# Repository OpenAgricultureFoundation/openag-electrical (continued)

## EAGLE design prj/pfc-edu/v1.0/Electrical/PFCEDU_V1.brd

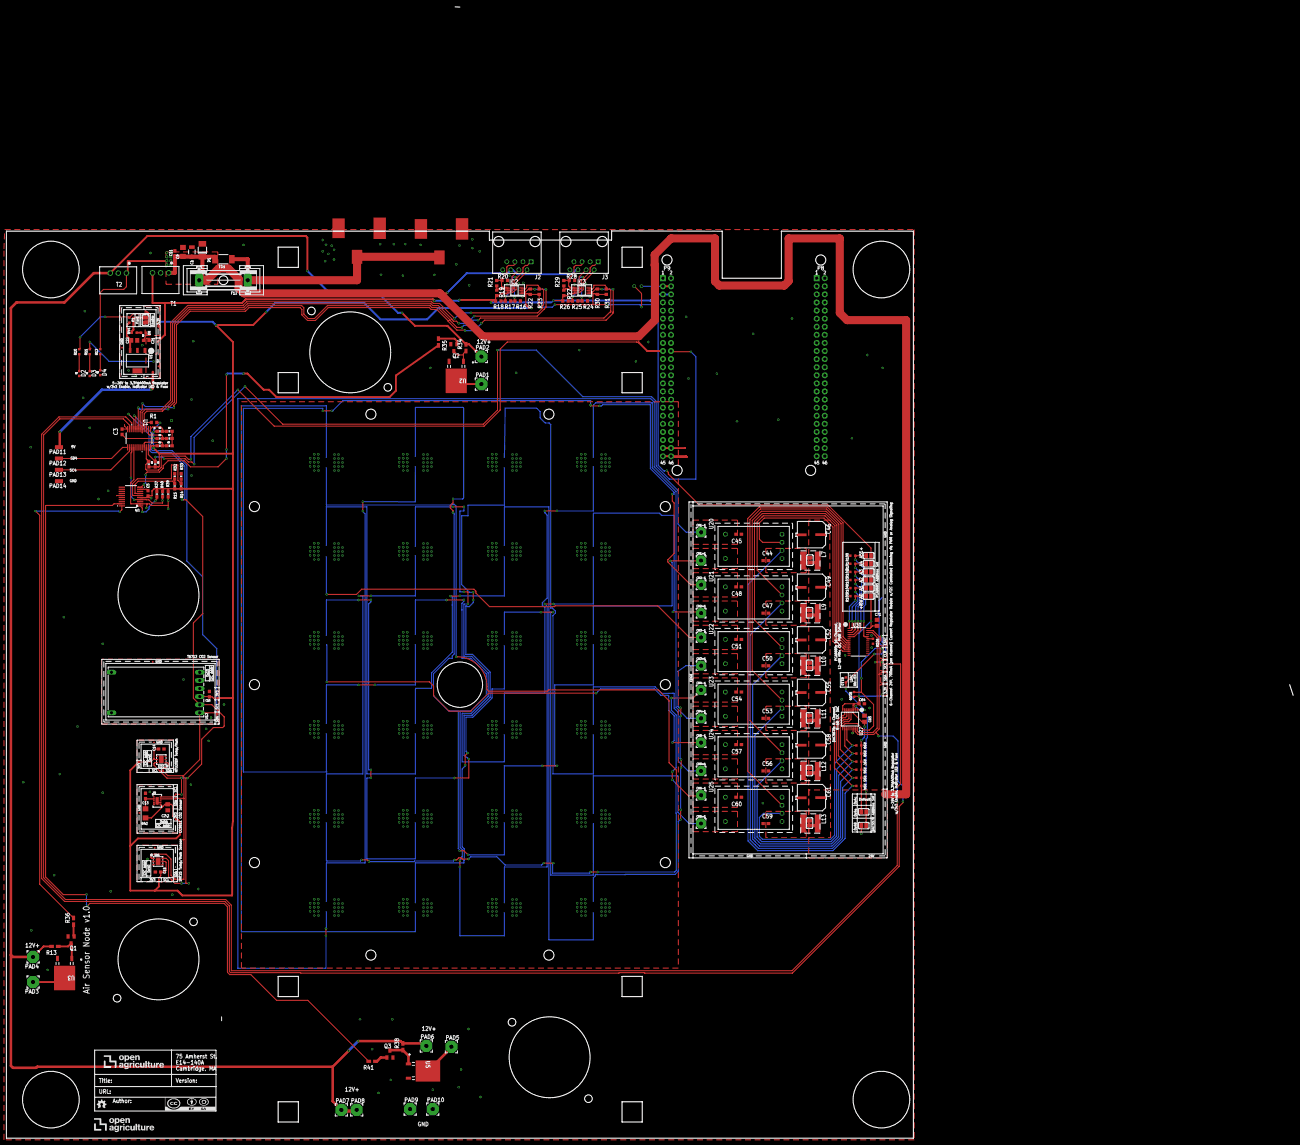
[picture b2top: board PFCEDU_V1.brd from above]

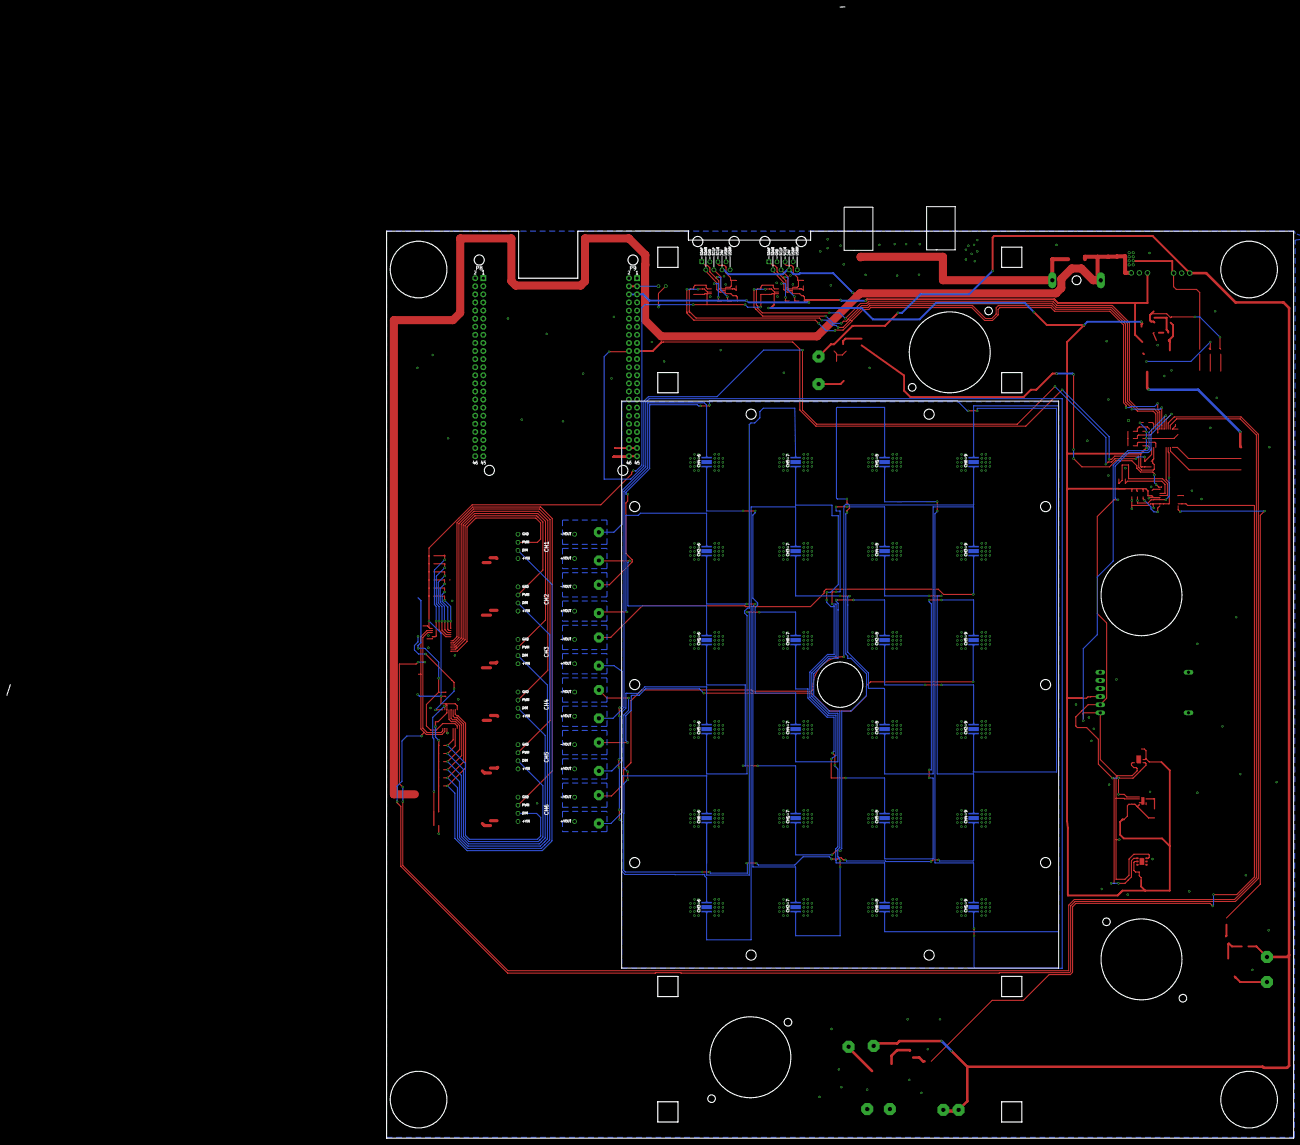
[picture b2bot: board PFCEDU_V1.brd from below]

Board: 2 copper layers, 284.7 x 284.8 mm, 221 parts (24 on the bottom side), 114 nets.

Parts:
ATTRIBUTES: DOCFIELD
C1: 4.7uF; CAP_C1206
C2\2, C65: 4.7uF; C0805
C3, C5, C11: .1uF; C0603@1
C9: 10uF; C1206
C13, C14, C15, C16, C21, C64: 0.1uF; C0603
C22, C71: 10uF; C0805
C44, C45, C47, C48, C50, C51, C53, C54, C56, C57, C59, C60: 10nF; C0603
C46, C49, C52, C55, C58, C61: 100uF; EEE-1HA101UP
CH1+1, CH1-1, CH2+1, CH2-1, CH3+1, CH3-1, CH4+1, CH4-1, CH5+1, CH5-1, CH6+1, CH6-1: 3,17/1,3
CH1-6, CH1-7, CH1-8, CH1-9, CH2-6, CH2-7, CH2-8, CH2-9, CH3-6, CH3-7, CH3-8, CH3-9, CH4-6, CH4-7, CH4-8, CH4-9, CH5-6, CH5-7, CH5-8, CH5-9, CH6-6, CH6-7, CH6-8, CH6-9: XP-E; CREE-XLAMP-XP-E
D1: SMAJ14A; DO-214AC
D2, D3, D4, D8: APT1608CGCK; CHIPLED_0603
F1: 0448.400MR; 0603
F11: SST 7; SS
F12: GSH15
IC2, IC3: PCA9615DP; SOP50P490X110-10N
J2, J3: 54602-908LF; OPENAG-V1-RJ45
L7, L9, L10, L11, L12, L13: 120uH; 74404064121
PAD1, PAD2, PAD3, PAD4, PAD5, PAD6, PAD7, PAD8, PAD9, PAD10: WIREPAD3,81/1,3; 3,81/1,3
PAD11, PAD12, PAD13, PAD14: SMD1,27-2,54
Q1, Q2, Q3: MMBT2222A; SOT23-BEC
R1, R22, R23, R30, R31: 10K; R0603
R2, R3, R4, R5, R6, R7, R8, R9, R14, R15, R32, R33, R37, R39, R40: 10K; 0603-RES
R10, R11, R12, R44: 100; RC0603N
R13, R34, R35, R36, R38, R41: R0805W
R16, R18, R19, R20, R24, R26, R27, R28: 600; R0603
R17, R21, R25, R29: 120; R0603
R42: 4.7K; R1206
R94, R95, R96, R97, R98, R99, R109: 1K; RC0603N
R100, R101, R102, R103, R104, R105, R106: 10K; RC0603N
R110: 0 OHM; RC0603N
SJ1: SOLDERJUMPER_REFLOW_NOPASTE
SJ_A18, SJ_A19, SJ_A20, SJ_A21, SJ_A22, SJ_A23, SJ_A24, SJ_A25, SJ_A26, SJ_A27, SJ_A28, SJ_A29, SJ_A34, SJ_A35: SOLDERJUMPER_REFLOW_NOPASTE
T1: R-78E5.0-1.0
T2: R-78E12.0-1.0; R-78E5.0-1.0
TP1, TP2, TP3, TP5, TP6, TP7, TP36, TP37, TP38, TP39, TP40, TP41, TP42, TP43, TP44, TP45, TP61, TP62, TP63: TPTP06R; TP06R
U1: TCA9548APWRPW24-M; PW24-M
U2, U3, U5: STD12NF06LT4; DPAK
U4: PCF8574APWRPW20-M; PW20-M
U9: CCS811
U10: HPP845E034R5; HTU20D(F)
U11: SHT25; SHT2X
U12: T6713-5K; T6713
U17: LM2937IMP3.3NOPB; MP04A
U20, U21, U22, U23, U24, U25: RCD-24-0.70/VREF; RCD-24-PINNED
U27: DAC5578SPW; TSSOP16
U30: PCA9685; TSSOP28
U$1, U$3: PJ-036AH
U$2: BEAGLE_BONE_BLACK_CAPE
U$9: OPENAG-LOGO-750-MIL

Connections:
24V_IN: F11.1, F12.1, U$1.1, U$3.1
!LDAC!: R110.2, U27.1
+3V3: C2\2.1, C3.1, C5.1, C14.1, C15.1, C16.1, C64.1, C65.1, C71.1, F1.2, IC2.1, IC3.1, R1.2, R2.2, R4.2, R6.2, R8.2, R9.2, R10.2, R14.2, R15.2, R22.2, R23.2, R30.2, R31.2, R37.2, R39.2, R40.2, R42.2, R94.1, R95.1, R96.1, R97.1, R98.1, R99.1, R109.1, SJ1.2, SJ_A18.1, SJ_A19.1, SJ_A20.1, SJ_A21.1, SJ_A22.1, SJ_A23.1, SJ_A34.1, TP5.TP, TP36.TP, TP41.TP, TP44.TP, TP63.TP, U1.24, U4.5, U9.6, U10.5, U11.5, U12.3, U27.3, U27.8, U30.28, U$2.P9.3, U$2.P9.4
+5V: C21.1, IC2.10, IC3.10, PAD11.1, R11.2, R18.1, R19.2, R26.1, R27.2, T1.3, TP62.TP, U17.1, U$2.P9.5, U$2.P9.6
+12V: PAD2.1, PAD4.1, PAD6.1, PAD7.1, PAD8.1, R13.2, R34.2, R38.2, T2.3
+24V: C1.1, C9.1, C11.1, C46.+, C49.+, C52.+, C55.+, C58.+, C61.+, D1.C, F11.2, F12.2, J2.24V(6), J3.24V(6), L7.1, L9.1, L10.1, L11.1, L12.1, L13.1, R12.2, SJ_A24.2, SJ_A25.2, SJ_A26.2, SJ_A27.2, SJ_A28.2, SJ_A29.2, T1.1, T2.1
A0: R105.2, SJ_A18.2, U30.1
A0_EXT_1: R4.1, R5.2, U1.1
A0_IO: R14.1, R33.2, U4.6
A1: R104.2, SJ_A19.2, U30.2
A1_EXT_1: R6.1, R7.2, U1.2
A1_IO: R15.1, R32.2, U4.7
A2: R103.2, SJ_A20.2, U30.3
A2_EXT_1: R2.1, R3.2, U1.21
A3: R102.2, SJ_A21.2, U30.4
A4: R101.2, SJ_A22.2, U30.5
A5: R100.2, SJ_A23.2, U30.24
ADDR0: SJ_A34.2, SJ_A35.2, U27.2
CH1+: CH1+1.1, CH1-6.A, CH1-6.A@1, U20.6
CH1-: C45.1, CH1-1.1, CH1-9.C, CH1-9.C@1, U20.5
CH2+: CH2+1.1, CH2-6.A, CH2-6.A@1, U21.6
CH2-: C48.1, CH2-1.1, CH2-9.C, CH2-9.C@1, U21.5
CH3+: CH3+1.1, CH3-6.A, CH3-6.A@1, U22.6
CH3-: C51.1, CH3-1.1, CH3-9.C, CH3-9.C@1, U22.5
CH4+: CH4+1.1, CH4-6.A, CH4-6.A@1, U23.6
CH4-: C54.1, CH4-1.1, CH4-9.C, CH4-9.C@1, U23.5
CH5+: CH5+1.1, CH5-6.A, CH5-6.A@1, U24.6
CH5-: C57.1, CH5-1.1, CH5-9.C, CH5-9.C@1, U24.5
CH6+: CH6+1.1, CH6-6.A, CH6-6.A@1, U25.6
CH6-: C60.1, CH6-1.1, CH6-9.C, CH6-9.C@1, U25.5
DAC_!CLR!: R109.2, U27.9
DIM1: R94.2, U20.2, U27.7
DIM2: R95.2, U21.2, U27.6
DIM3: R96.2, U22.2, U27.5
DIM4: R97.2, U23.2, U27.4
DIM5: R98.2, U24.2, U27.10
DIM6: R99.2, U25.2, U27.11
DSCLM0: IC2.6, J2.DSCLM(5), R20.2, R21.1
DSCLM1: IC3.6, J3.DSCLM(5), R28.2, R29.1
DSCLP0: IC2.7, J2.DSCLP(4), R19.1, R21.2
DSCLP1: IC3.7, J3.DSCLP(4), R27.1, R29.2
DSDAM0: IC2.9, J2.DSDAM(2), R16.1, R17.2
DSDAM1: IC3.9, J3.DSDAM(2), R24.1, R25.2
DSDAP0: IC2.8, J2.DSDAP(1), R17.1, R18.2
DSDAP1: IC3.8, J3.DSDAP(1), R25.1, R26.2
GND: C1.2, C2\2.2, C3.2, C5.2, C9.2, C11.2, C13.2, C14.2, C15.2, C16.2, C21.2, C22.2, C44.2, C45.2, C46.-, C47.2, C48.2, C49.-, C50.2, C51.2, C52.-, C53.2, C54.2, C55.-, C56.2, C57.2, C58.-, C59.2, C60.2, C61.-, C64.2, C65.2, C71.2, D1.A, D2.C, D3.C, D4.C, D8.C, IC2.5, IC3.5, J2.GND(3), J3.GND(3), PAD9.1, PAD10.1, PAD14.1, Q1.E, Q2.E, Q3.E, R3.1, R5.1, R7.1, R16.2, R20.1, R24.2, R28.1, R32.1, R33.1, R100.1, R101.1, R102.1, R103.1, R104.1, R105.1, R106.2, R110.1, SJ_A35.1, T1.2, T2.2, TP3.TP, TP37.TP, TP40.TP, TP45.TP, TP61.TP, U1.12, U2.2, U3.2, U4.9, U4.15, U5.2, U9.1, U9.7, U9.EP, U10.2, U11.2, U12.4, U12.6, U17.2, U17.4, U20.4, U21.4, U22.4, U23.4, U24.4, U25.4, U27.14, U30.14, U30.25, U$1.2, U$1.3, U$2.P8.1, U$2.P8.2, U$2.P9.1, U$2.P9.2, U$2.P9.43, U$2.P9.44, U$2.P9.45, U$2.P9.46, U$3.2, U$3.3
MOS1: PAD3.1, U3.3
MOS2: PAD1.1, U2.3
MOS3: PAD5.1, U5.3
unnamed: D3.A, R11.1
unnamed: D4.A, R12.1
unnamed: Q1.C, R13.1, U3.1
unnamed: Q1.B, R36.1
unnamed: D2.A, R10.1
unnamed: R37.1, U4.1
unnamed: Q2.C, R34.1, U2.1
unnamed: Q2.B, R35.1
unnamed: Q3.C, R38.1, U5.1
unnamed: Q3.B, R41.1
unnamed: CH2-8.C, CH2-8.C@1, CH2-9.A, CH2-9.A@1
unnamed: CH2-7.C, CH2-7.C@1, CH2-8.A, CH2-8.A@1
unnamed: CH2-6.C, CH2-6.C@1, CH2-7.A, CH2-7.A@1
unnamed: CH4-8.C, CH4-8.C@1, CH4-9.A, CH4-9.A@1
unnamed: CH4-7.C, CH4-7.C@1, CH4-8.A, CH4-8.A@1
unnamed: CH4-6.C, CH4-6.C@1, CH4-7.A, CH4-7.A@1
unnamed: CH6-8.C, CH6-8.C@1, CH6-9.A, CH6-9.A@1
unnamed: CH6-7.C, CH6-7.C@1, CH6-8.A, CH6-8.A@1
unnamed: C44.1, L7.2, SJ_A24.1, U20.1
unnamed: C47.1, L9.2, SJ_A25.1, U21.1
unnamed: C50.1, L10.2, SJ_A26.1, U22.1
unnamed: C53.1, L11.2, SJ_A27.1, U23.1
unnamed: U9.4, U9.5
unnamed: C13.1, R42.1, U9.2
unnamed: C56.1, L12.2, SJ_A28.1, U24.1
unnamed: C59.1, L13.2, SJ_A29.1, U25.1
unnamed: CH6-6.C, CH6-6.C@1, CH6-7.A, CH6-7.A@1
unnamed: CH1-8.C, CH1-8.C@1, CH1-9.A, CH1-9.A@1
unnamed: CH1-7.C, CH1-7.C@1, CH1-8.A, CH1-8.A@1
unnamed: CH1-6.C, CH1-6.C@1, CH1-7.A, CH1-7.A@1
unnamed: CH3-8.C, CH3-8.C@1, CH3-9.A, CH3-9.A@1
unnamed: CH3-7.C, CH3-7.C@1, CH3-8.A, CH3-8.A@1
unnamed: CH3-6.C, CH3-6.C@1, CH3-7.A, CH3-7.A@1
unnamed: CH5-8.C, CH5-8.C@1, CH5-9.A, CH5-9.A@1
unnamed: CH5-7.C, CH5-7.C@1, CH5-8.A, CH5-8.A@1
unnamed: CH5-6.C, CH5-6.C@1, CH5-7.A, CH5-7.A@1
unnamed: D8.A, R44.1
unnamed: C22.1, F1.1, U17.3
OE: R106.1, U30.23
P0_IO: R35.2, U4.10
P6_IO: R41.2, U4.19
P7_IO: R36.2, U4.20
PWM1: U20.3, U30.12
PWM2: U21.3, U30.11
PWM3: U22.3, U30.10
PWM4: U23.3, U30.9
PWM5: U24.3, U30.8
PWM6: U25.3, U30.7
REG_3V3_400MA: R44.2, SJ1.1
RESET1: R1.1, U1.3
SC0: IC2.4, R23.1, U1.5
SC1: IC3.4, R31.1, U1.7
SC2: TP1.TP, TP7.TP, TP39.TP, TP43.TP, U1.9, U9.10, U10.6, U11.6, U12.2
SC3: U1.11, U27.16, U30.26
SC4: PAD13.1, U1.14
SC5: R39.1, U1.16, U4.2
SCL: R8.1, U1.22, U$2.P9.19
SD0: IC2.2, R22.1, U1.4
SD1: IC3.2, R30.1, U1.6
SD2: TP2.TP, TP6.TP, TP38.TP, TP42.TP, U1.8, U9.9, U10.1, U11.1, U12.1
SD3: U1.10, U27.15, U30.27
SD4: PAD12.1, U1.13
SD5: R40.1, U1.15, U4.4
SDA: R9.1, U1.23, U$2.P9.20
T1: CH1-6.THERM, CH1-7.THERM, CH1-8.THERM, CH1-9.THERM, CH2-6.THERM, CH2-7.THERM, CH2-8.THERM, CH2-9.THERM, CH3-6.THERM, CH3-7.THERM, CH3-8.THERM, CH3-9.THERM, CH4-6.THERM, CH4-7.THERM, CH4-8.THERM, CH4-9.THERM, CH5-6.THERM, CH5-7.THERM, CH5-8.THERM, CH5-9.THERM, CH6-6.THERM, CH6-7.THERM, CH6-8.THERM, CH6-9.THERM

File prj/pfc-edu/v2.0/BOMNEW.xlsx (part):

Part | Value | Device | Package | Description | 3D_PACKAGE | ALLIED_NUMBER | AUTHOR | DESCRIPTION.1 | HEIGHT | MANUFACTURER_NAME | MANUFACTURER_PART_NUMBER | MF | MPN | OC_FARNELL | OC_NEWARK | OTHER_PART_NUMBER | POPULATE | PROD_ID | RS_PART_NUMBER | SUPPLIER_NAME | TITLE | TP_SIGNAL_NAME | URL | VALUE.1 | VENDOR | VER | VERIFIED | Column1
ATTRIBUTES |  | DOCFIELD | DOCFIELD | DOCUMENT FIELD |  |  | DP | PFC EDU |  |  |  |  |  |  |  |  |  |  |  |  | PFC EDU |  | https://github.com/OpenAgInitiative/ |  |  | 2
C1 | 4.7uF | 4.7UF-C1206C475K5PACTU | CAP_C1206 | Kemet - C1206C475K5PACTU - CAP CER 4.7UF 50V X5R 1206 |  |  |  |  |  |  |  |  |  |  |  |  | YES |  |  |  |  |  |  | 4.7uF |  |  | NO
C2\2 | 4.7uF | 4.7UF-CL21A475KBQNNNE | C0805 | Samsung - CL21A475KBQNNNE - CAP CER 4.7UF 50V X5R 0805 |  |  |  |  |  |  |  |  |  |  |  |  | YES |  |  |  |  |  |  | 4.7uF |  |  | NO
C3 | .1uF | C-USC0603 | C0603@1 | CAPACITOR, American symbol
C5 | .1uF | C-USC0603 | C0603@1 | CAPACITOR, American symbol
C9 | 10uF | 10UF-CL31B106KBHNNNE | C1206 | Samsung - CL31B106KBHNNNE - CAP CER 10UF 50V X7R 1206 |  |  |  |  |  |  |  |  |  |  |  |  | YES |  |  |  |  |  |  | 10uF |  |  | NO
C11 | .1uF | C-USC0603 | C0603@1 | CAPACITOR, American symbol
C13 | 0.1uF | 0.1UF-C0603C104K5RACTU | C0603 | Kemet - C0603C104K5RACTU - CAP CER 0.1UF 50V X7R 0603 |  |  |  |  |  |  |  |  |  |  |  |  | YES |  |  |  |  |  |  | 0.1uF |  |  | NO
C14 | 0.1uF | 0.1UF-C0603C104K5RACTU | C0603 | Kemet - C0603C104K5RACTU - CAP CER 0.1UF 50V X7R 0603 |  |  |  |  |  |  |  |  |  |  |  |  | YES |  |  |  |  |  |  | 0.1uF |  |  | NO
C15 | 0.1uF | 0.1UF-C0603C104K5RACTU | C0603 | Kemet - C0603C104K5RACTU - CAP CER 0.1UF 50V X7R 0603 |  |  |  |  |  |  |  |  |  |  |  |  | YES |  |  |  |  |  |  | 0.1uF |  |  | NO
C16 | 0.1uF | 0.1UF-C0603C104K5RACTU | C0603 | Kemet - C0603C104K5RACTU - CAP CER 0.1UF 50V X7R 0603 |  |  |  |  |  |  |  |  |  |  |  |  | YES |  |  |  |  |  |  | 0.1uF |  |  | NO
C21 | 0.1uF | 0.1UF-C0603C104K5RACTU | C0603 | Kemet - C0603C104K5RACTU - CAP CER 0.1UF 50V X7R 0603 |  |  |  |  |  |  |  |  |  |  |  |  | YES |  |  |  |  |  |  | 0.1uF |  |  | NO
C22 | 10uF | 10UF-GMK212BBJ106KG-T | C0805 | Taiyo Yuden - GMK212BBJ106KG-T - CAP CER 10UF 35V X5R 0805 |  |  |  |  |  |  |  |  |  |  |  |  | YES |  |  |  |  |  |  | 10uF |  |  | NO
C44 | 10nF | 10NF-C0603C103K5RACTU | C0603 | KEMET - C0603C103K5RACTU - CAP CER 10000PF 50V X7R 0603 |  |  |  |  |  |  |  |  |  |  |  |  | YES |  |  |  |  |  |  | 10nF |  |  | NO
C45 | 10nF | 10NF-C0603C103K5RACTU | C0603 | KEMET - C0603C103K5RACTU - CAP CER 10000PF 50V X7R 0603 |  |  |  |  |  |  |  |  |  |  |  |  | YES |  |  |  |  |  |  | 10nF |  |  | NO
C46 | 100uF | 100UF-EEE-1HA101UP | EEE-1HA101UP | Panasonic - EEE-1HA101UP - ELECTROLYTIC CAP ALUM 100UF 20% 50V SMD |  |  |  |  |  |  |  |  |  |  |  |  | YES |  |  |  |  |  |  | 100uF |  |  | NO
C47 | 10nF | 10NF-C0603C103K5RACTU | C0603 | KEMET - C0603C103K5RACTU - CAP CER 10000PF 50V X7R 0603 |  |  |  |  |  |  |  |  |  |  |  |  | YES |  |  |  |  |  |  | 10nF |  |  | NO
C48 | 10nF | 10NF-C0603C103K5RACTU | C0603 | KEMET - C0603C103K5RACTU - CAP CER 10000PF 50V X7R 0603 |  |  |  |  |  |  |  |  |  |  |  |  | YES |  |  |  |  |  |  | 10nF |  |  | NO
C49 | 100uF | 100UF-EEE-1HA101UP | EEE-1HA101UP | Panasonic - EEE-1HA101UP - ELECTROLYTIC CAP ALUM 100UF 20% 50V SMD |  |  |  |  |  |  |  |  |  |  |  |  | YES |  |  |  |  |  |  | 100uF |  |  | NO
C50 | 10nF | 10NF-C0603C103K5RACTU | C0603 | KEMET - C0603C103K5RACTU - CAP CER 10000PF 50V X7R 0603 |  |  |  |  |  |  |  |  |  |  |  |  | YES |  |  |  |  |  |  | 10nF |  |  | NO
C51 | 10nF | 10NF-C0603C103K5RACTU | C0603 | KEMET - C0603C103K5RACTU - CAP CER 10000PF 50V X7R 0603 |  |  |  |  |  |  |  |  |  |  |  |  | YES |  |  |  |  |  |  | 10nF |  |  | NO
C52 | 100uF | 100UF-EEE-1HA101UP | EEE-1HA101UP | Panasonic - EEE-1HA101UP - ELECTROLYTIC CAP ALUM 100UF 20% 50V SMD |  |  |  |  |  |  |  |  |  |  |  |  | YES |  |  |  |  |  |  | 100uF |  |  | NO
C53 | 10nF | 10NF-C0603C103K5RACTU | C0603 | KEMET - C0603C103K5RACTU - CAP CER 10000PF 50V X7R 0603 |  |  |  |  |  |  |  |  |  |  |  |  | YES |  |  |  |  |  |  | 10nF |  |  | NO
C54 | 10nF | 10NF-C0603C103K5RACTU | C0603 | KEMET - C0603C103K5RACTU - CAP CER 10000PF 50V X7R 0603 |  |  |  |  |  |  |  |  |  |  |  |  | YES |  |  |  |  |  |  | 10nF |  |  | NO
C55 | 100uF | 100UF-EEE-1HA101UP | EEE-1HA101UP | Panasonic - EEE-1HA101UP - ELECTROLYTIC CAP ALUM 100UF 20% 50V SMD |  |  |  |  |  |  |  |  |  |  |  |  | YES |  |  |  |  |  |  | 100uF |  |  | NO
C56 | 10nF | 10NF-C0603C103K5RACTU | C0603 | KEMET - C0603C103K5RACTU - CAP CER 10000PF 50V X7R 0603 |  |  |  |  |  |  |  |  |  |  |  |  | YES |  |  |  |  |  |  | 10nF |  |  | NO
C57 | 10nF | 10NF-C0603C103K5RACTU | C0603 | KEMET - C0603C103K5RACTU - CAP CER 10000PF 50V X7R 0603 |  |  |  |  |  |  |  |  |  |  |  |  | YES |  |  |  |  |  |  | 10nF |  |  | NO
C58 | 100uF | 100UF-EEE-1HA101UP | EEE-1HA101UP | Panasonic - EEE-1HA101UP - ELECTROLYTIC CAP ALUM 100UF 20% 50V SMD |  |  |  |  |  |  |  |  |  |  |  |  | YES |  |  |  |  |  |  | 100uF |  |  | NO
C59 | 10nF | 10NF-C0603C103K5RACTU | C0603 | KEMET - C0603C103K5RACTU - CAP CER 10000PF 50V X7R 0603 |  |  |  |  |  |  |  |  |  |  |  |  | YES |  |  |  |  |  |  | 10nF |  |  | NO
C60 | 10nF | 10NF-C0603C103K5RACTU | C0603 | KEMET - C0603C103K5RACTU - CAP CER 10000PF 50V X7R 0603 |  |  |  |  |  |  |  |  |  |  |  |  | YES |  |  |  |  |  |  | 10nF |  |  | NO
C61 | 100uF | 100UF-EEE-1HA101UP | EEE-1HA101UP | Panasonic - EEE-1HA101UP - ELECTROLYTIC CAP ALUM 100UF 20% 50V SMD |  |  |  |  |  |  |  |  |  |  |  |  | YES |  |  |  |  |  |  | 100uF |  |  | NO
C64 | 0.1uF | 0.1UF-C0603C104K5RACTU | C0603 | Kemet - C0603C104K5RACTU - CAP CER 0.1UF 50V X7R 0603 |  |  |  |  |  |  |  |  |  |  |  |  | YES |  |  |  |  |  |  | 0.1uF |  |  | NO
C65 | 4.7uF | 4.7UF-CL21A475KBQNNNE | C0805 | Samsung - CL21A475KBQNNNE - CAP CER 4.7UF 50V X5R 0805 |  |  |  |  |  |  |  |  |  |  |  |  | YES |  |  |  |  |  |  | 4.7uF |  |  | NO
C71 | 10uF | 10UF-GMK212BBJ106KG-T | C0805 | Taiyo Yuden - GMK212BBJ106KG-T - CAP CER 10UF 35V X5R 0805 |  |  |  |  |  |  |  |  |  |  |  |  | YES |  |  |  |  |  |  | 10uF |  |  | NO
CH1+1 |  | 3,17/1,3 | 3,17/1,3 | THROUGH-HOLE PAD
CH1-1 |  | 3,17/1,3 | 3,17/1,3 | THROUGH-HOLE PAD
CH1-6 | XP-E | LED_W/THERM-XP-E | CREE-XLAMP-XP-E
CH1-7 | XP-E | LED_W/THERM-XP-E | CREE-XLAMP-XP-E
CH1-8 | XP-E | LED_W/THERM-XP-E | CREE-XLAMP-XP-E
CH1-9 | XP-E | LED_W/THERM-XP-E | CREE-XLAMP-XP-E
CH2+1 |  | 3,17/1,3 | 3,17/1,3 | THROUGH-HOLE PAD
CH2-1 |  | 3,17/1,3 | 3,17/1,3 | THROUGH-HOLE PAD
CH2-6 | XP-E | LED_W/THERM-XP-E | CREE-XLAMP-XP-E
CH2-7 | XP-E | LED_W/THERM-XP-E | CREE-XLAMP-XP-E
CH2-8 | XP-E | LED_W/THERM-XP-E | CREE-XLAMP-XP-E
CH2-9 | XP-E | LED_W/THERM-XP-E | CREE-XLAMP-XP-E
CH3+1 |  | 3,17/1,3 | 3,17/1,3 | THROUGH-HOLE PAD
CH3-1 |  | 3,17/1,3 | 3,17/1,3 | THROUGH-HOLE PAD
CH3-6 | XP-E | LED_W/THERM-XP-E | CREE-XLAMP-XP-E
CH3-7 | XP-E | LED_W/THERM-XP-E | CREE-XLAMP-XP-E
CH3-8 | XP-E | LED_W/THERM-XP-E | CREE-XLAMP-XP-E
CH3-9 | XP-E | LED_W/THERM-XP-E | CREE-XLAMP-XP-E
CH4+1 |  | 3,17/1,3 | 3,17/1,3 | THROUGH-HOLE PAD
CH4-1 |  | 3,17/1,3 | 3,17/1,3 | THROUGH-HOLE PAD
CH4-6 | XP-E | LED_W/THERM-XP-E | CREE-XLAMP-XP-E
CH4-7 | XP-E | LED_W/THERM-XP-E | CREE-XLAMP-XP-E
CH4-8 | XP-E | LED_W/THERM-XP-E | CREE-XLAMP-XP-E
CH4-9 | XP-E | LED_W/THERM-XP-E | CREE-XLAMP-XP-E
CH5+1 |  | 3,17/1,3 | 3,17/1,3 | THROUGH-HOLE PAD
CH5-1 |  | 3,17/1,3 | 3,17/1,3 | THROUGH-HOLE PAD
CH5-6 | XP-E | LED_W/THERM-XP-E | CREE-XLAMP-XP-E
CH5-7 | XP-E | LED_W/THERM-XP-E | CREE-XLAMP-XP-E
CH5-8 | XP-E | LED_W/THERM-XP-E | CREE-XLAMP-XP-E
CH5-9 | XP-E | LED_W/THERM-XP-E | CREE-XLAMP-XP-E
CH6+1 |  | 3,17/1,3 | 3,17/1,3 | THROUGH-HOLE PAD
CH6-1 |  | 3,17/1,3 | 3,17/1,3 | THROUGH-HOLE PAD
CH6-6 | XP-E | LED_W/THERM-XP-E | CREE-XLAMP-XP-E
CH6-7 | XP-E | LED_W/THERM-XP-E | CREE-XLAMP-XP-E
CH6-8 | XP-E | LED_W/THERM-XP-E | CREE-XLAMP-XP-E
CH6-9 | XP-E | LED_W/THERM-XP-E | CREE-XLAMP-XP-E
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
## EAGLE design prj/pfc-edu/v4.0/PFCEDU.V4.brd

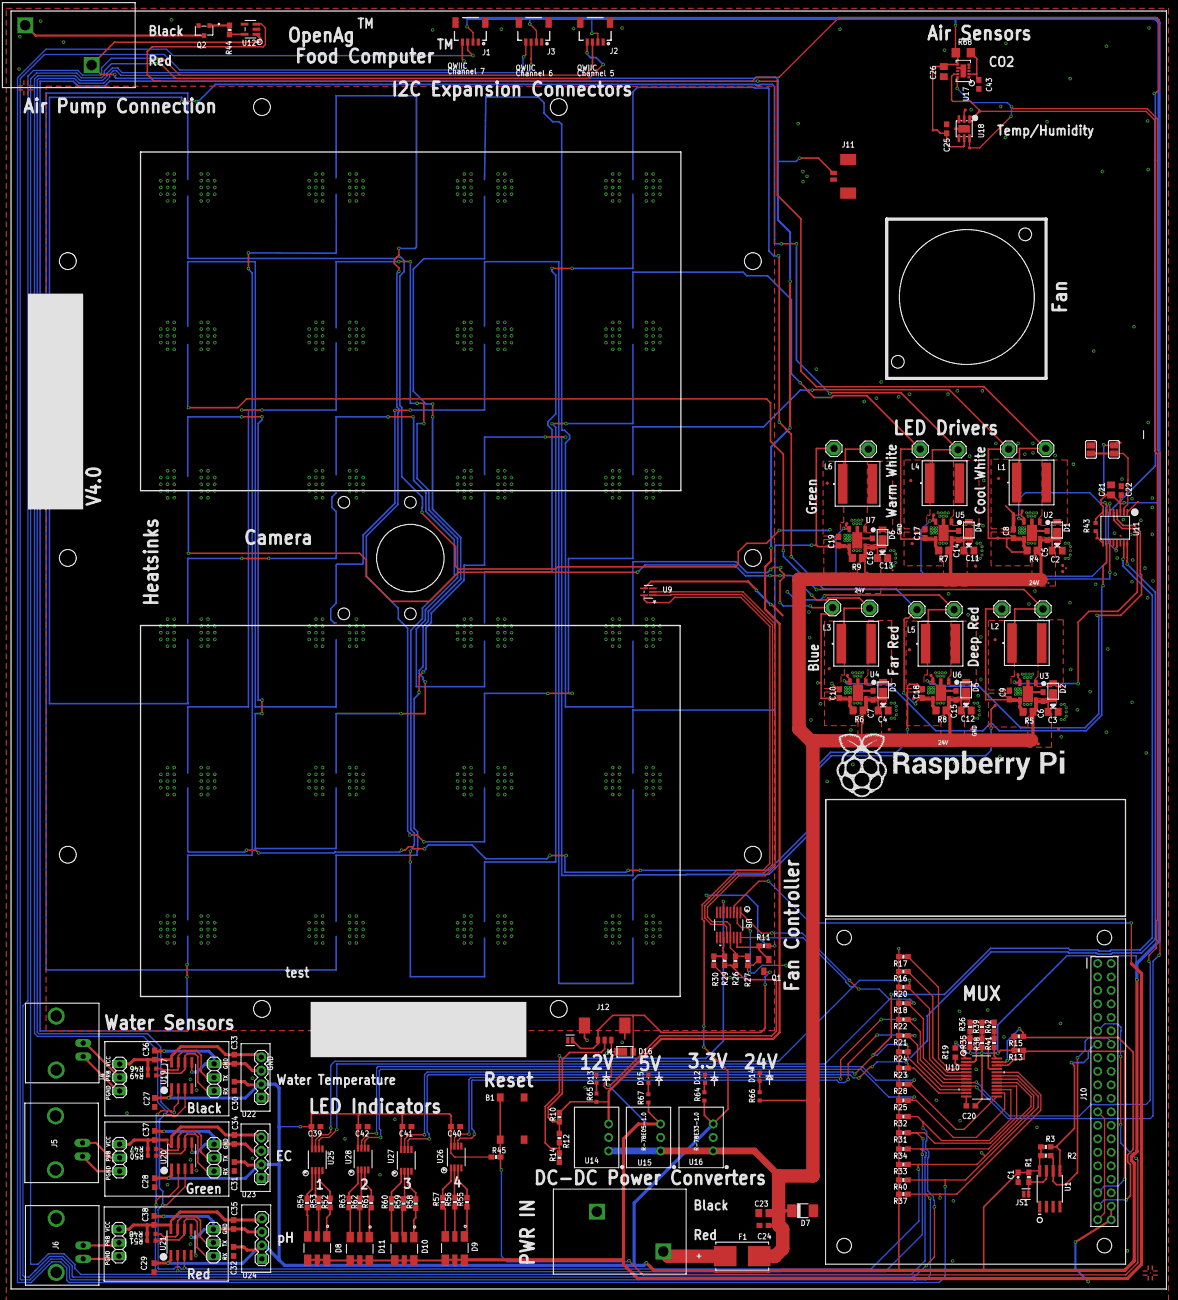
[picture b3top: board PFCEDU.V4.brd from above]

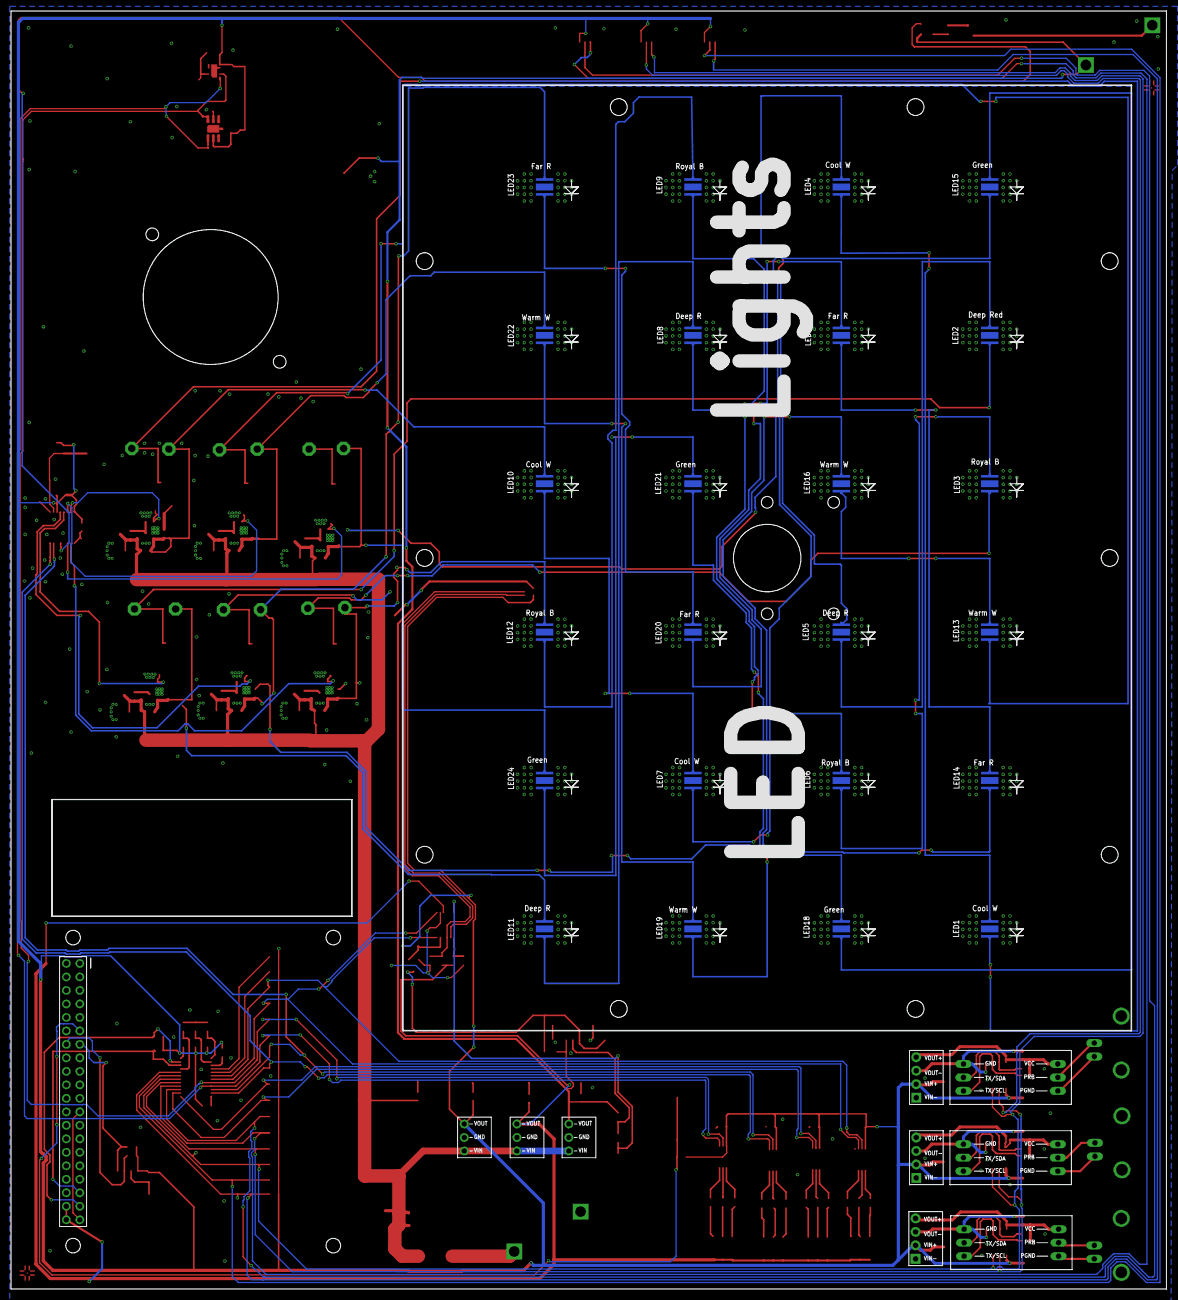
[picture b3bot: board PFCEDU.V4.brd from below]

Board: 2 copper layers, 217.6 x 240.6 mm, 262 parts (24 on the bottom side), 138 nets.

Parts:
A1: PTS645
C1: 0.1uF; CAP-0603
C2, C3, C4, C11, C12, C13: 10uF; C0805
C5, C6, C7, C8, C9, C10, C14, C15, C16, C17, C18, C19, C22, C25, C27, C28, C29, C30, C31, C32, C33, C34, C35, C36, C37, C38, C39, C40, C41, C42, C43: 0.1uF; C0603
C20, C24: .1uF; C0603@1
C21, C23, C26: 4.7uF; C0805
D1, D2, D3, D4, D5, D6, D16: SBR2A40P1-7; POWERDI123
D7: SMAJ14A; DO-214AC
D8, D9, D10, D11: QBLP679E-RGB; LED_QBLP679E-RGB
D12, D13, D14, D15: APT1608; CHIPLED_0603
DRILEGEND: DRILEGEND
F1: 0154005.DR; 0154SERIES
J1, J2, J3: Qwiic Right Angle; 1X04_1MM_RA
J4, J5, J6: 5227161-9; BNC-5227161
J7, J8, J9: ATLAS-STAMP
J10: PFCEDU_V7_PI4_AI_CONNECTORS_2X20-RPI-NOFIRST
J11: MOLEX_2P_1.25MM
J12: MOLEX_3P_1.25MM
JS1, JS2: 1X02-SJ-NO
L1, L2, L3, L4, L5, L6: NR8040T101M; IND_TAIYO_NR8040
LED1, LED2, LED3, LED4, LED5, LED6, LED7, LED8, LED9, LED10, LED11, LED12, LED13, LED14, LED15, LED16, LED17, LED18, LED19, LED20, LED21, LED22, LED23, LED24: XP-E; CREE-XLAMP-XP-E
LSP1, LSP2, LSP3, LSP4, LSP5, LSP6, LSP7, LSP8, LSP9, LSP10, LSP11, LSP12: SE14
Q1: MMBT2222A; SOT23-BEC
Q2: BSS138K; SOT-23
R1: 1K; RES-0603
R2: 2.2kΩ; RES-0603
R3: 2.2KΩ; RES-0603
R4, R5, R6, R7, R8, R9: 6.34 ohm; R0805
R10, R12, R26, R27, R29, R30, R45: 10k; 0603-RES
R11, R14: 4.7KΩ; 0603-RES
R13: 2.2K; 0603-RES
R15, R16, R17, R18, R20, R21, R22, R23, R24, R25, R28, R31, R32, R33, R34, R37, R40: 2.2k; 0603-RES
R19: 10K; R0603
R35, R38, R41: 10K; 0603-RES
R36, R39, R42: NP; 0603-RES
R43: 1K; RC0603N
R44: 10; 0603-RES
R46, R47, R48, R49, R50, R51: 2.2KΩ; RC0603N
R52, R53, R54, R55, R56, R57, R58, R59, R60, R61, R62, R63: 240; 0603-RES
R64: 160; RC0603N
R65: 600; RC0603N
R66: 1200; RC0603N
R67: 260; RC0603N
R68: 10K; R1206
SJ1, SJ2: SJ1
TP38, TP39, TP40, TP41, TP112, TP113, TP114, TP115, TP116, TP117, TP118, TP119, TP120, TP121, TP122, TP123, TP124, TP125, TP126, TP127, TP128, TP129, TP130, TP131, TP132, TP133, TP134, TP135, TP136, TP137, TP138, TP139, TP140, TP141: TPTP06R; TP06R
TP99, TP100, TP101, TP104, TP105, TP106, TP107: TPTP04R; TP04R
U1: 24LC32A; SO08-EIAJ
U2, U3, U4, U5, U6, U7: AL8861
U8: ADT7470ARQZ-REEL; RQ_16
U9: TMP05AKSZ-500RL7; KS_5
U10: TCA9548APWRPW24-M; PW24-M
U11: DAC5578; TSSOP16
U12: UCC27517DBVR; DBV5
U14: R-78E12-1.0; R-78E5.0-1.0
U15: R-78E05-1.0; R-78E5.0-1.0
U16: R-78E33-1.0; R-78E5.0-1.0
U17: CCS811
U18: SHT25; SHT2X
U19, U20, U21: ISO1540; D8
U22, U23, U24: RM-3.33.3S; RM3.33.3S-SIP4
U25, U26, U27, U28: PCA9633DP1SOT505-1-L; SOT505-1-L
U$1, U$2: PASSER-CIRCLE
W11, W12: PHOENIX_2P

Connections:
24V_IN: F1.1, W12.1
!LDAC!: TP104.1, U11.1
+3V3: C1.1, C20.1, C21.1, C22.1, C25.1, C26.1, C27.1, C28.1, C29.1, C30.1, C31.1, C32.1, C39.2, C40.2, C41.2, C42.2, J1.2, J2.2, J3.2, R1.2, R2.2, R3.2, R11.2, R13.2, R15.2, R16.2, R17.2, R18.2, R19.2, R20.2, R21.2, R22.2, R23.2, R24.2, R25.2, R28.2, R31.2, R32.2, R33.2, R34.2, R35.2, R37.2, R38.2, R40.2, R41.2, R43.1, R45.1, R64.2, R68.2, SJ1.1, TP41.TP, TP100.1, U1.8, U9.5, U10.24, U11.3, U11.8, U16.3, U17.6, U18.5, U19.1, U20.1, U21.1, U22.2, U23.2, U24.2, U25.8, U26.8, U27.8, U28.8
+5V: D8.4, D8.5, D8.6, D9.4, D9.5, D9.6, D10.4, D10.5, D10.6, D11.4, D11.5, D11.6, J10.2, J10.4, R26.1, R29.1, R67.2, U8.3, U15.3
+12V: D16.-, J11.2, J12.1, R10.2, R65.2, U12.1, U14.3, W11.2
+24V: C2.1, C3.1, C4.1, C5.1, C6.1, C7.1, C11.1, C12.1, C13.1, C14.1, C15.1, C16.1, C23.1, C24.1, D1.-, D2.-, D3.-, D4.-, D5.-, D6.-, D7.C, F1.2, R4.2, R5.2, R6.2, R7.2, R8.2, R9.2, R66.2, TP99.1, TP113.TP, TP118.TP, TP123.TP, TP128.TP, TP133.TP, TP138.TP, U2.5, U3.5, U4.5, U5.5, U6.5, U7.5, U14.1, U15.1, U16.1
A0_EXT_1: R35.1, R36.2, U10.1
A1_EXT_1: R38.1, R39.2, U10.2
A2_EXT_1: R41.1, R42.2, U10.21
ADDR0: SJ1.2, SJ2.2, U11.2
BUTTON: A1.P$1, A1.P$2, J10.29, R45.2
CH1+: C8.2, LED10.A, LED10.A@1, LSP1.MP, R4.1, TP115.TP, U2.4
CH1-: C8.1, L1.1, LED1.C, LED1.C@1, LSP2.MP, TP112.TP
CH2+: C17.2, LED22.A, LED22.A@1, LSP7.MP, R7.1, TP120.TP, U5.4
CH2-: C17.1, L4.1, LED13.C, LED13.C@1, LSP8.MP, TP117.TP
CH3+: C9.2, LED11.A, LED11.A@1, LSP3.MP, R5.1, TP125.TP, U3.4
CH3-: C9.1, L2.1, LED2.C, LED2.C@1, LSP4.MP, TP122.TP
CH4+: C18.2, LED23.A, LED23.A@1, LSP9.MP, R8.1, TP130.TP, U6.4
CH4-: C18.1, L5.1, LED14.C, LED14.C@1, LSP10.MP, TP127.TP
CH5+: C10.2, LED12.A, LED12.A@1, LSP5.MP, R6.1, TP135.TP, U4.4
CH5-: C10.1, L3.1, LED3.C, LED3.C@1, LSP6.MP, TP132.TP
CH6+: C19.2, LED24.A, LED24.A@1, LSP11.MP, R9.1, TP140.TP, U7.4
CH6-: C19.1, L6.1, LED15.C, LED15.C@1, LSP12.MP, TP137.TP
DAC_!CLR!: R43.2, TP105.1, U11.9
F1_PWM: Q1.B, R11.1, U8.15
FAN_NEG: D16.+, J12.5, JS2.1, Q1.C
GATE: Q2.1, R44.2
GND: A1.P$3, A1.P$4, C1.2, C2.2, C3.2, C4.2, C5.2, C6.2, C7.2, C11.2, C12.2, C13.2, C14.2, C15.2, C16.2, C20.2, C21.2, C22.2, C23.2, C24.2, C25.2, C26.2, C27.2, C28.2, C29.2, C30.2, C31.2, C32.2, C39.1, C40.1, C41.1, C42.1, C43.2, D7.A, D12.C, D13.C, D14.C, D15.C, J1.1, J2.1, J3.1, J10.6, J10.9, J10.14, J10.20, J10.25, J10.30, J10.34, J10.39, J11.1, J11.3, J11.4, J12.3, J12.4, JS1.1, JS2.2, Q1.E, Q2.2, R14.1, R27.2, R30.2, R36.1, R39.1, R42.1, SJ2.1, TP40.TP, TP101.1, TP106.1, TP107.1, TP114.TP, TP119.TP, TP124.TP, TP129.TP, TP134.TP, TP139.TP, U1.1, U1.2, U1.3, U1.4, U2.2, U2.44, U3.2, U3.44, U4.2, U4.44, U5.2, U5.44, U6.2, U6.44, U7.2, U7.44, U8.2, U9.4, U10.12, U11.14, U12.2, U12.4, U14.2, U15.2, U16.2, U17.1, U17.7, U17.EP, U18.2, U19.4, U20.4, U21.4, U22.1, U23.1, U24.1, U25.5, U26.5, U27.5, U28.5, W12.2
ID_SC: J10.28, R2.1, U1.6
ID_SD: J10.27, R3.1, U1.5
ISO_3V3_2: C33.1, C36.1, J7.4, R46.2, R49.2, U19.8, U22.4
ISO_3V3_3: C34.1, C37.1, J8.4, R47.2, R50.2, U20.8, U23.4
ISO_3V3_4: C35.1, C38.1, J9.4, R48.2, R51.2, U21.8, U24.4
ISO_GND_2: C33.2, C36.2, J7.3, U19.5, U22.3
ISO_GND_3: C34.2, C37.2, J8.3, U20.5, U23.3
ISO_GND_4: C35.2, C38.2, J9.3, U21.5, U24.3
ISO_SCL_2: J7.1, R49.1, U19.6
ISO_SCL_3: J8.1, R50.1, U20.6
ISO_SCL_4: J9.1, R51.1, U21.6
ISO_SDA_2: J7.2, R46.1, U19.7
ISO_SDA_3: J8.2, R47.1, U20.7
ISO_SDA_4: J9.2, R48.1, U21.7
LX: D1.+, L1.2, U2.1
LX_2: D4.+, L4.2, U5.1
LX_3: D2.+, L2.2, U3.1
LX_4: D5.+, L5.2, U6.1
LX_5: D3.+, L3.2, U4.1
LX_6: D6.+, L6.2, U7.1
unnamed: R54.2, U25.1
unnamed: D15.A, R67.1
unnamed: R53.2, U25.2
unnamed: D14.A, R66.1
unnamed: R52.2, U25.3
unnamed: D8.3, R54.1
unnamed: D8.2, R53.1
unnamed: D8.1, R52.1
unnamed: R63.2, U28.1
unnamed: R62.2, U28.2
unnamed: R61.2, U28.3
unnamed: D12.A, R64.1
unnamed: D11.3, R63.1
unnamed: D11.2, R62.1
unnamed: D11.1, R61.1
unnamed: R60.2, U27.1
unnamed: R59.2, U27.2
unnamed: R58.2, U27.3
unnamed: D10.3, R60.1
unnamed: D10.2, R59.1
unnamed: D10.1, R58.1
unnamed: R57.2, U26.1
unnamed: R56.2, U26.2
unnamed: R55.2, U26.3
unnamed: D9.3, R57.1
unnamed: D9.2, R56.1
unnamed: D9.1, R55.1
unnamed: LED13.A, LED13.A@1, LED16.C, LED16.C@1
unnamed: LED16.A, LED16.A@1, LED19.C, LED19.C@1
unnamed: LED19.A, LED19.A@1, LED22.C, LED22.C@1
unnamed: LED14.A, LED14.A@1, LED17.C, LED17.C@1
unnamed: LED17.A, LED17.A@1, LED20.C, LED20.C@1
unnamed: LED20.A, LED20.A@1, LED23.C, LED23.C@1
unnamed: LED15.A, LED15.A@1, LED18.C, LED18.C@1
unnamed: LED18.A, LED18.A@1, LED21.C, LED21.C@1
unnamed: R29.2, R30.1, U8.11
unnamed: D13.A, R65.1
unnamed: R12.2, R14.2, U8.6
unnamed: J10.1, J10.17
unnamed: U17.4, U17.5
unnamed: C43.1, R68.1, U17.2
unnamed: LED21.A, LED21.A@1, LED24.C, LED24.C@1
unnamed: LED1.A, LED1.A@1, LED4.C, LED4.C@1
unnamed: LED4.A, LED4.A@1, LED7.C, LED7.C@1
unnamed: R44.1, U12.5
unnamed: JS1.2, R1.1, U1.7
unnamed: LED7.A, LED7.A@1, LED10.C, LED10.C@1
unnamed: LED2.A, LED2.A@1, LED5.C, LED5.C@1
unnamed: LED5.A, LED5.A@1, LED8.C, LED8.C@1
unnamed: LED8.A, LED8.A@1, LED11.C, LED11.C@1
unnamed: LED3.A, LED3.A@1, LED6.C, LED6.C@1
unnamed: LED6.A, LED6.A@1, LED9.C, LED9.C@1
unnamed: LED9.A, LED9.A@1, LED12.C, LED12.C@1
PGND_2: J4.GND, J7.6
PGND_3: J5.GND, J8.6
PGND_4: J6.GND, J9.6
PRB_2: J4.S, J7.5
PRB_3: J5.S, J8.5
PRB_4: J6.S, J9.5
PUMP: U11.13, U12.3
PUMP_GND: Q2.3, W11.1
RESET1: R19.1, U10.3
SC0: R16.1, U10.5
SC1: R18.1, U8.1, U10.7, U25.6
SC2: R21.1, TP39.TP, U10.9, U17.10, U18.6, U26.6
SC3: R23.1, U10.11, U11.16, U27.6
SC4: R25.1, U10.14, U28.6
SC5: J2.4, R31.1, U10.16
SC6: J3.4, R33.1, U10.18, U19.3, U20.3, U21.3
SC7: J1.4, R37.1, U10.20
SCL: J10.5, R13.1, U10.22
SD0: R17.1, U10.4
SD1: R20.1, U8.16, U10.6, U25.7
SD2: R22.1, TP38.TP, U10.8, U17.9, U18.1, U26.7
SD3: R24.1, U10.10, U11.15, U27.7
SD4: R28.1, U10.13, U28.7
SD5: J2.3, R32.1, U10.15
SD6: J3.3, R34.1, U10.17, U19.2, U20.2, U21.2
SD7: J1.3, R40.1, U10.19
SDA: J10.3, R15.1, U10.23
T1: LED1.THERM, LED2.THERM, LED3.THERM, LED4.THERM, LED5.THERM, LED6.THERM, LED7.THERM, LED8.THERM, LED9.THERM, LED10.THERM, LED11.THERM, LED12.THERM, LED13.THERM, LED14.THERM, LED15.THERM, LED16.THERM, LED17.THERM, LED18.THERM, LED19.THERM, LED20.THERM, LED21.THERM, LED22.THERM, LED23.THERM, LED24.THERM
TACH: J12.2, R10.1, R12.1
TMPIN: U8.12, U9.1
TMPSTART: R26.2, R27.1, U8.13, U9.2
VSET: TP116.TP, U2.3, U11.7
VSET_2: TP121.TP, U5.3, U11.6
VSET_3: TP126.TP, U3.3, U11.5
VSET_4: TP131.TP, U6.3, U11.4
VSET_5: TP136.TP, U4.3, U11.10
VSET_6: TP141.TP, U7.3, U11.11

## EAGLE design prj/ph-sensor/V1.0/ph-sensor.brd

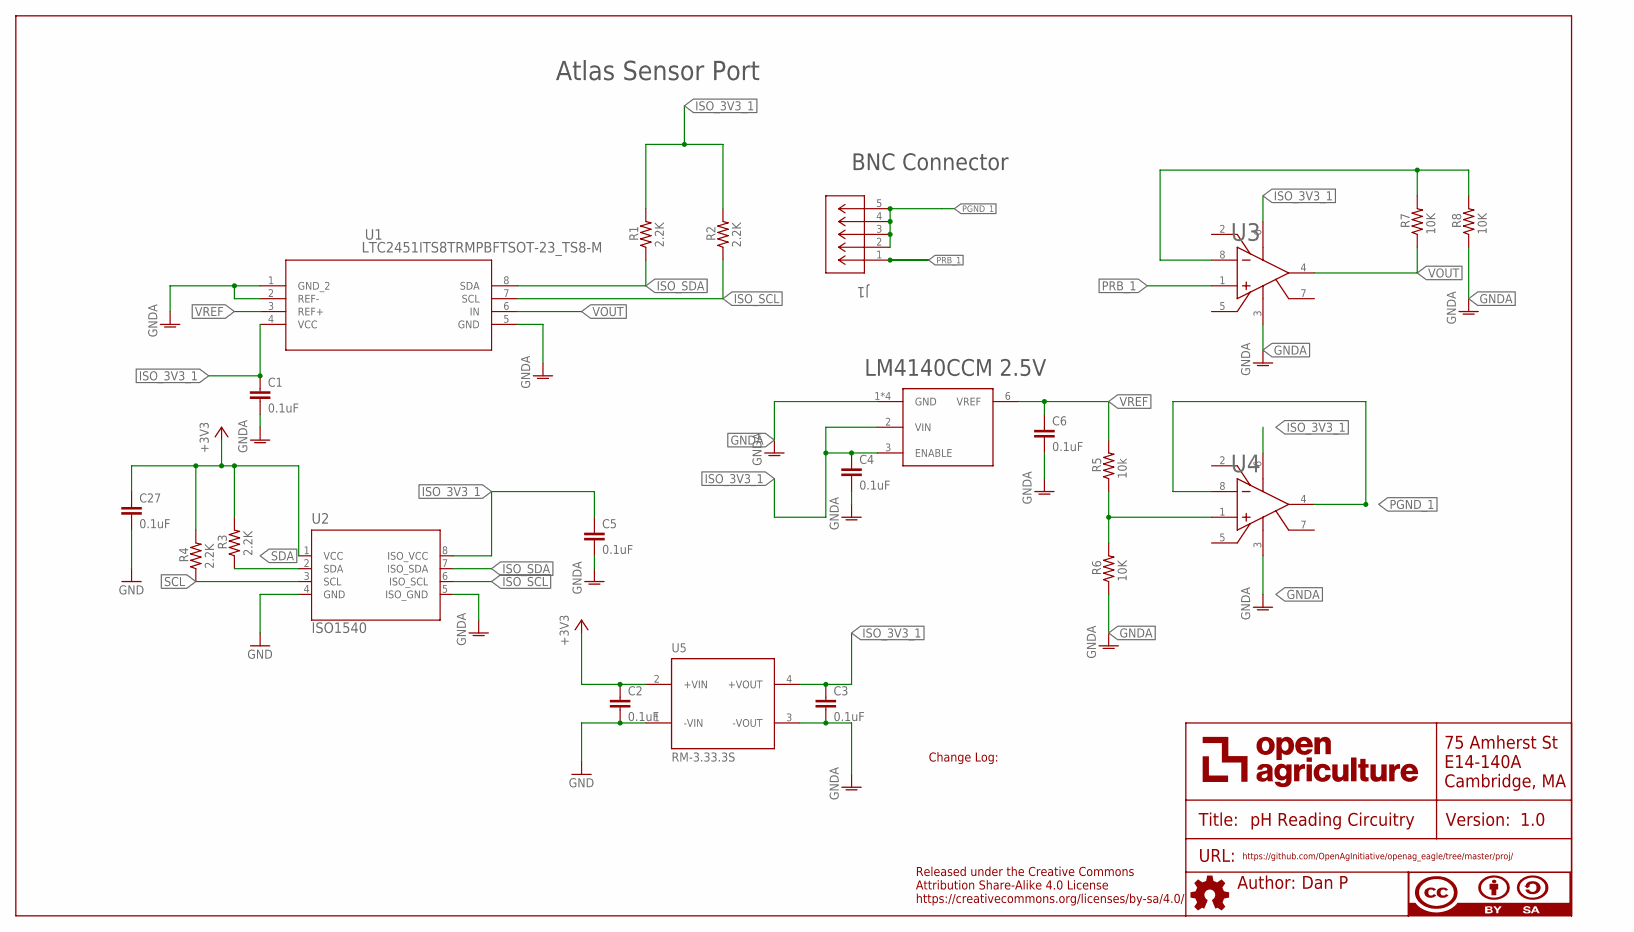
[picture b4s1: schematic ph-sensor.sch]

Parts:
C1, C2, C3, C4, C5, C6, C27: 0.1uF; C0603
J1: 5-1634503-1; CONN5_5-1634503-1
R1, R2, R3, R4: 2.2K; RC0603N
R5: 10k; RC0603N
R6, R7, R8: 10K; RC0603N
U1: LTC2451ITS8TRMPBFTSOT-23_TS8-M; TSOT-23_TS8-M
U2: ISO1540; D8
U3, U4: LMP7721MA/NOPBM08A-M; M08A-M
U5: RM-3.33.3S; RM3.33.3S-SIP4
U$5: LM4140CCM_2.5V; SO08

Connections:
+3V3: C2.1, C27.1, R3.2, R4.2, U2.1 (VCC), U5.2 (+VIN)
GND: C2.2, C27.2, U2.4 (GND), U5.1 (-VIN)
GNDA: C1.2, C3.2, C4.2, C5.2, C6.2, R6.1, R8.1, U1.1 (GND_2), U1.2 (REF-), U1.5 (GND), U2.5 (ISO_GND), U3.3 (V-), U4.3 (V-), U5.3 (-VOUT), U$5.1 (GND), U$5.4 (GND), U$5.7 (GND), U$5.8 (GND)
ISO_3V3_1: C1.1, C3.1, C4.1, C5.1, R1.2, R2.2, U1.4 (VCC), U2.8 (ISO_VCC), U3.6 (V+), U4.6 (V+), U5.4 (+VOUT), U$5.2 (VIN), U$5.3 (ENABLE)
ISO_SCL: R2.1, U1.7 (SCL), U2.6 (ISO_SCL)
ISO_SDA: R1.1, U1.8 (SDA), U2.7 (ISO_SDA)
unnamed: R5.1, R6.2, U4.1 (IN+)
unnamed: R7.2, R8.2, U3.8 (IN-)
PGND_1: J1.2, J1.3, J1.4, J1.5, U4.4 (OUT), U4.8 (IN-)
PRB_1: J1.1, U3.1 (IN+)
SCL: R4.1, U2.3 (SCL)
SDA: R3.1, U2.2 (SDA)
VOUT: R7.1, U1.6 (IN), U3.4 (OUT)
VREF: C6.1, R5.2, U1.3 (REF+), U$5.6 (VREF)

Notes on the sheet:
BNC Connector
Atlas Sensor Port
LM4140CCM 2.5V
Change Log:
Released under the Creative Commons Attribution Share-Alike 4.0 License https://creativecommons.org/licenses/by-sa/4.0/
